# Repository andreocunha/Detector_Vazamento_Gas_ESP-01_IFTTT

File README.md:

# Detector_Vazamento_Gas_Esp_IFTTT
Simples detector de vazamento de gás e aumento de temperatura que utiliza ESP-01 e envia um alerta pelo IFTTT

<h1 align="center">
    
</h1>

Passo a passo para configurar o IFTTT para envir o alerta para o celular. Primeiro entre no site oficial do IFTTT e crie uma conta. Baixe o app deles no celular também.

<br>
No site, depois de logar, selecione "Webhooks"

<br>
Clique no "+" depois do "if"

<br>
Busque por "Webhooks" e selecione ele

<br>
Escreva um nome para o seu evento

<br>
Depois clique no outro "+" e busque por "Notifictions"

<br>
Escreve a mensagem que você queira que mostre na notificação do celular.

<br>
Por fim, vá para Home, Webhooks, e clique em Documentations. Lá terá a sua "key" que deverá ser adcionada no código do ESP-01.

<br>
<br>
Feito pelo grupo PET Engenharia de Computação - UFES<br/>

André Oliveira Cunha - :wave: [Linkedin](https://www.linkedin.com/in/andr%C3%A9-oliveira-cunha-b26b3a156/)

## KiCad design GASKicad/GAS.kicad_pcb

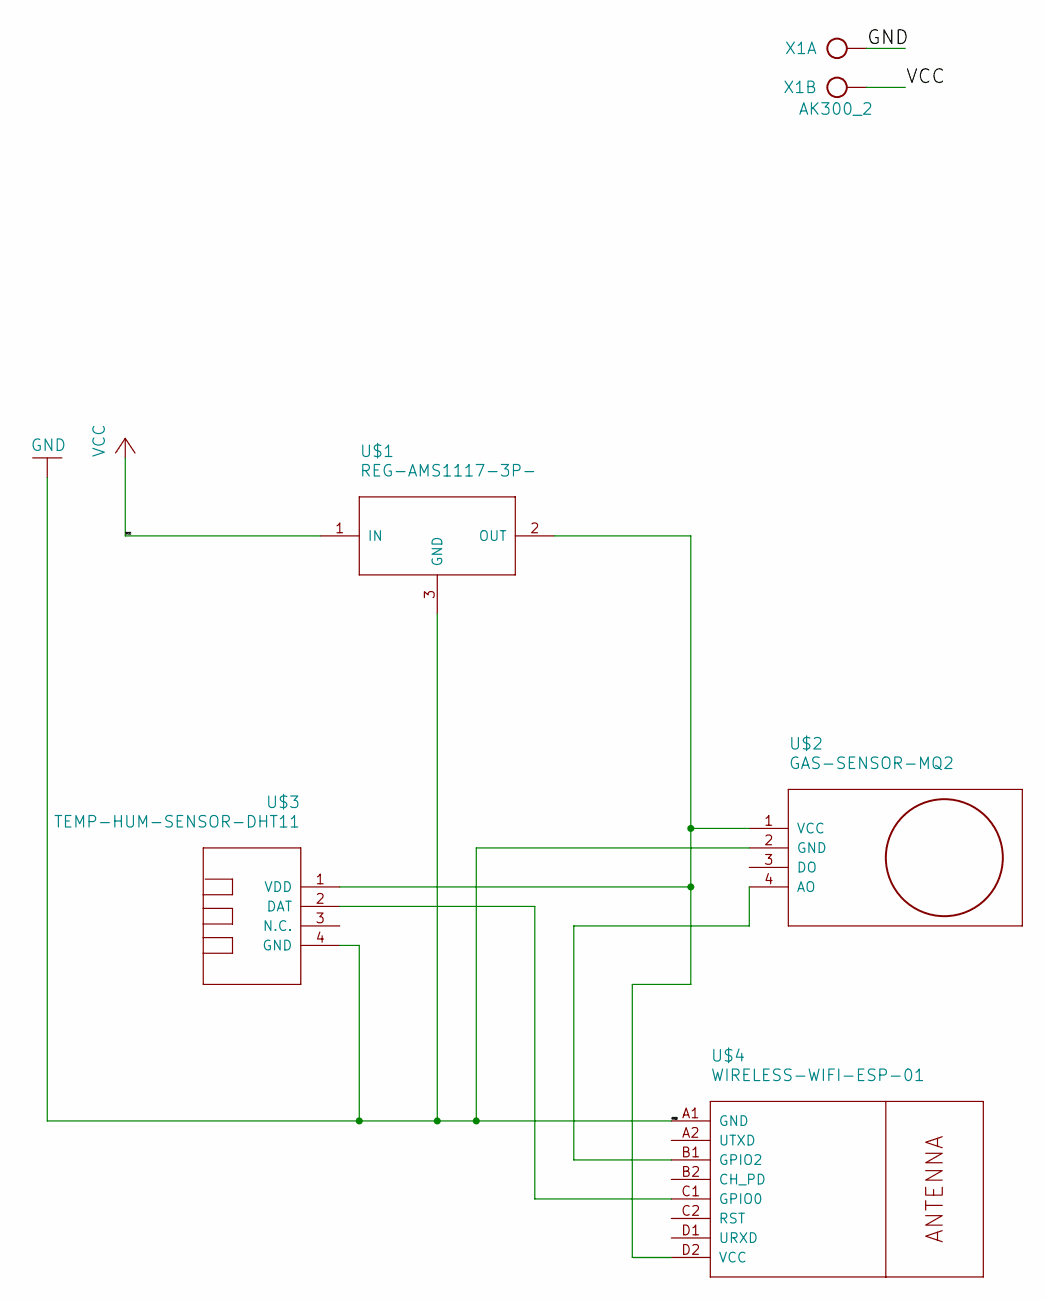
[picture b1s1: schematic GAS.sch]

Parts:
U$1: REG-AMS1117-3P-; REG-AMS1117-3P
U$2: GAS-SENSOR-MQ2
U$3: TEMP-HUM-SENSOR-DHT11
U$4: WIRELESS-WIFI-ESP-01
X1: AK300_2

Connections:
GND: U$1.3 (GND), U$2.2 (GND), U$3.4 (GND), U$4.A1 (GND), X1.1
unnamed: U$1.2 (OUT), U$2.1 (VCC), U$3.1 (VDD), U$4.D2 (VCC)
unnamed: U$2.4 (AO), U$4.B1 (GPIO2)
unnamed: U$3.2 (DAT), U$4.C1 (GPIO0)
VCC: U$1.1 (IN), X1.2

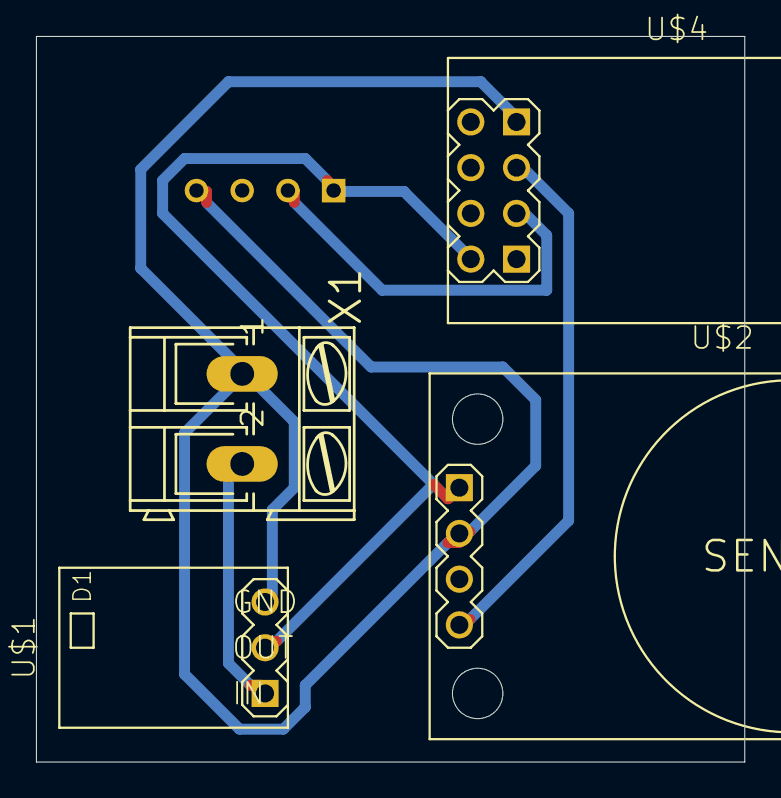
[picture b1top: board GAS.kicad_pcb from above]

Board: 2 copper layers, 39.3 x 40.3 mm, 5 parts (0 on the bottom side), 5 nets.

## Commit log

2020-08-01 Detector de vazamento de gás
2020-08-01 imagens
2020-08-16 Adição do sensor de temperatura
